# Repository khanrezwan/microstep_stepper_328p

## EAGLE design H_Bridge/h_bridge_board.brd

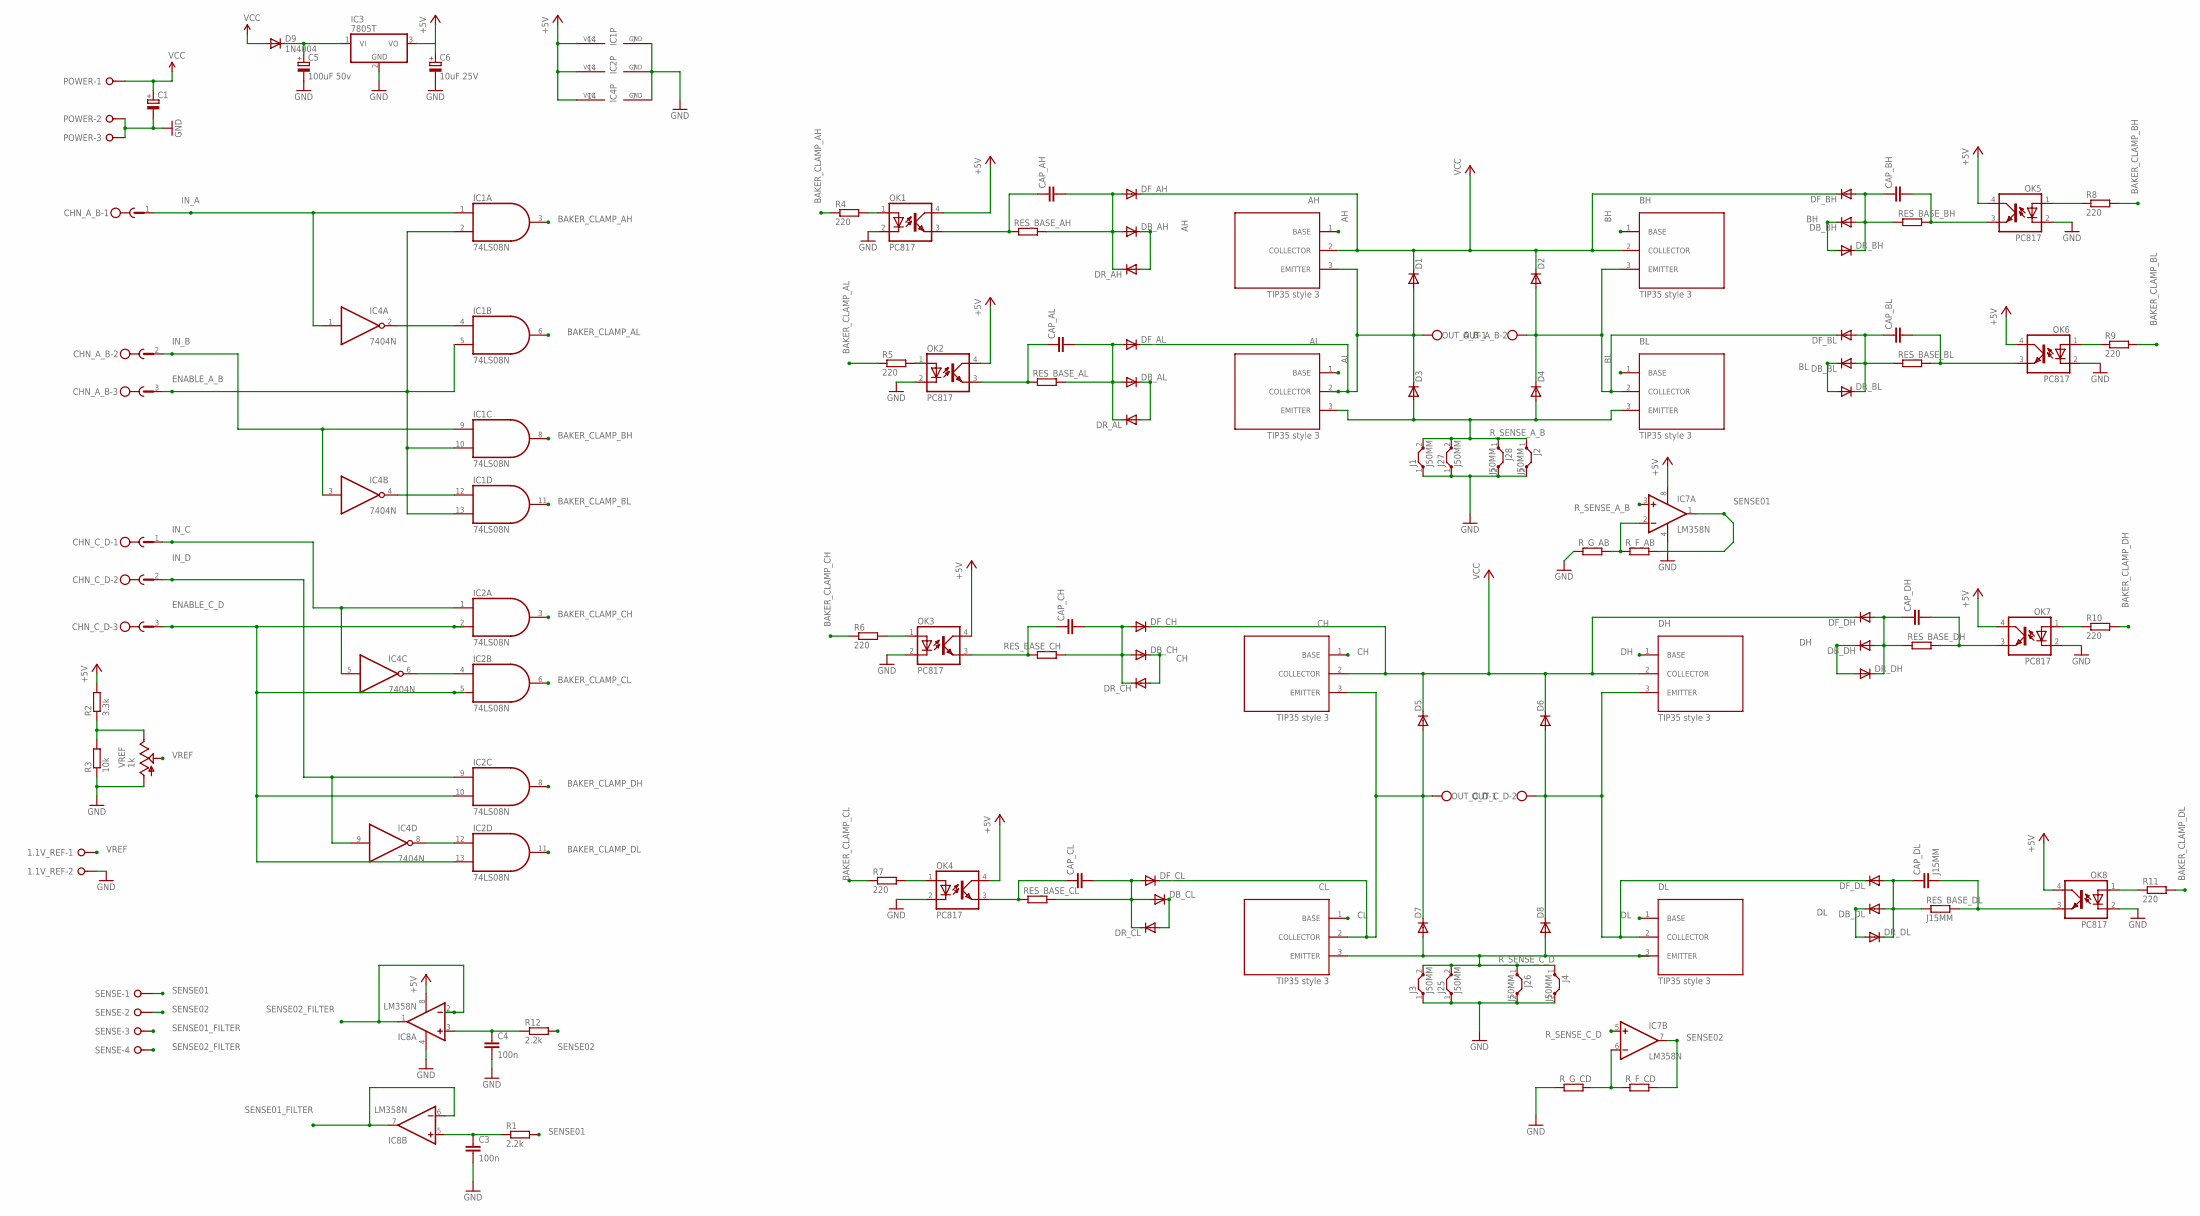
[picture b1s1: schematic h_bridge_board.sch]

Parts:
1.1V_REF: W237-02P; W237-132
AH: TIP35_STYLE3; P-TO247
AL: TIP35_STYLE3; P-TO247
BH: TIP35_STYLE3; P-TO247
BL: TIP35_STYLE3; P-TO247
C1: CPOL-EUE5-10.5; E5-10,5
C3, C4: 100n; C050-030X075
C5: 100uF 50v; E5-10,5
C6: 10uF 25V; E2,5-6
CAP_AH: C-EU050-030X075; C050-030X075
CAP_AL: C-EU050-030X075; C050-030X075
CAP_BH: C-EU050-030X075; C050-030X075
CAP_BL: C-EU050-030X075; C050-030X075
CAP_CH: C-EU050-030X075; C050-030X075
CAP_CL: C-EU050-030X075; C050-030X075
CAP_DH: C-EU050-030X075; C050-030X075
CAP_DL: J15MM; C050-030X075
CH: TIP35_STYLE3; P-TO247
CHN_A_B: W232-3
CHN_C_D: W232-3
CL: TIP35_STYLE3; P-TO247
D1, D2, D3, D4, D5, D6, D7, D8: DIODE-DO27-15; DO27-15
D9: 1N4004; DO41-10
DB_AH: DIODE-DO27-15; DO27-15
DB_AL: DIODE-DO27-15; DO27-15
DB_BH: DIODE-DO27-15; DO27-15
DB_BL: DIODE-DO27-15; DO27-15
DB_CH: DIODE-DO27-15; DO27-15
DB_CL: DIODE-DO27-15; DO27-15
DB_DH: DIODE-DO27-15; DO27-15
DB_DL: DIODE-DO27-15; DO27-15
DF_AH: DIODE-DO27-15; DO27-15
DF_AL: DIODE-DO27-15; DO27-15
DF_BH: DIODE-DO27-15; DO27-15
DF_BL: DIODE-DO27-15; DO27-15
DF_CH: DIODE-DO27-15; DO27-15
DF_CL: DIODE-DO27-15; DO27-15
DF_DH: DIODE-DO27-15; DO27-15
DF_DL: DIODE-DO27-15; DO27-15
DH: TIP35_STYLE3; P-TO247
DL: TIP35_STYLE3; P-TO247
DR_AH: DIODE-DO27-15; DO27-15
DR_AL: DIODE-DO27-15; DO27-15
DR_BH: DIODE-DO27-15; DO27-15
DR_BL: DIODE-DO27-15; DO27-15
DR_CH: DIODE-DO27-15; DO27-15
DR_CL: DIODE-DO27-15; DO27-15
DR_DH: DIODE-DO27-15; DO27-15
DR_DL: DIODE-DO27-15; DO27-15
IC1, IC2: 74LS08N; DIL14
IC3: 7805T; TO220H
IC4: 7404N; DIL14
IC7, IC8: LM358N; DIL08
J1, J2, J3, J4, J25, J26, J27, J28: J50MM; 50
OK1, OK2, OK3, OK4, OK5, OK6, OK7, OK8: PC817; DIL04
OUT_A_B: W237-102
OUT_C_D: W237-102
POWER: W237-3E
R1, R12: 2.2k; 0207/10
R2: 3.3k; 0207/10
R3: 10k; 0207/10
R4, R5, R6, R7, R8, R9, R10, R11: 220; 0207/10
RES_BASE_AH: R-EU_0207/10; 0207/10
RES_BASE_AL: R-EU_0207/10; 0207/10
RES_BASE_BH: R-EU_0207/10; 0207/10
RES_BASE_BL: R-EU_0207/10; 0207/10
RES_BASE_CH: R-EU_0207/10; 0207/10
RES_BASE_CL: R-EU_0207/10; 0207/10
RES_BASE_DH: R-EU_0207/10; 0207/10
RES_BASE_DL: J15MM; 0207/10
R_F_AB: R-EU_0207/10; 0207/10
R_F_CD: R-EU_0207/10; 0207/10
R_G_AB: R-EU_0207/10; 0207/10
R_G_CD: R-EU_0207/10; 0207/10
SENSE: W237-04P; W237-4P
VREF: 1k; B25U

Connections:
+5V: C6.+, IC1.14 (VCC), IC2.14 (VCC), IC3.3 (VO), IC4.14 (VCC), IC7.8 (V+), IC8.8 (V+), OK1.4 (COL), OK2.4 (COL), OK3.4 (COL), OK4.4 (COL), OK5.4 (COL), OK6.4 (COL), OK7.4 (COL), OK8.4 (COL), R2.2
AH: AH.1 (BASE), DB_AH.C, DR_AH.A
AL: AL.1 (BASE), DB_AL.C, DR_AL.A
BAKER_CLAMP_AH: IC1.3 (O), R4.1
BAKER_CLAMP_AL: IC1.6 (O), R5.1
BAKER_CLAMP_BH: IC1.8 (O), R8.2
BAKER_CLAMP_BL: IC1.11 (O), R9.2
BAKER_CLAMP_CH: IC2.3 (O), R6.1
BAKER_CLAMP_CL: IC2.6 (O), R7.1
BAKER_CLAMP_DH: IC2.8 (O), R10.2
BAKER_CLAMP_DL: IC2.11 (O), R11.2
BH: BH.1 (BASE), DB_BH.C, DR_BH.A
BL: BL.1 (BASE), DB_BL.C, DR_BL.A
CH: CH.1 (BASE), DB_CH.C, DR_CH.A
CL: CL.1 (BASE), DB_CL.C, DR_CL.A
DH: DB_DH.C, DH.1 (BASE), DR_DH.A
DL: DB_DL.C, DL.1 (BASE), DR_DL.A
ENABLE_A_B: CHN_A_B.3, IC1.2 (I1), IC1.5 (I1), IC1.10 (I1), IC1.13 (I1)
ENABLE_C_D: CHN_C_D.3, IC2.2 (I1), IC2.5 (I1), IC2.10 (I1), IC2.13 (I1)
GND: 1.1V_REF.2, C1.-, C3.2, C4.2, C5.-, C6.-, IC1.7 (GND), IC2.7 (GND), IC3.2 (GND), IC4.7 (GND), IC7.4 (V-), IC8.4 (V-), J1.1, J2.2, J3.1, J4.2, J25.1, J26.2, J27.1, J28.2, OK1.2 (C), OK2.2 (C), OK3.2 (C), OK4.2 (C), OK5.2 (C), OK6.2 (C), OK7.2 (C), OK8.2 (C), POWER.2, POWER.3, R3.1, R_G_AB.1, R_G_CD.1, VREF.A
IN_A: CHN_A_B.1, IC1.1 (I0), IC4.1 (I)
IN_B: CHN_A_B.2, IC1.9 (I0), IC4.3 (I)
IN_C: CHN_C_D.1, IC2.1 (I0), IC4.5 (I)
IN_D: CHN_C_D.2, IC2.9 (I0), IC4.9 (I)
unnamed: IC1.12 (I0), IC4.4 (O)
unnamed: R2.1, R3.2, VREF.E
unnamed: C5.+, D9.C, IC3.1 (VI)
unnamed: CAP_AL.2, DB_AL.A, DF_AL.A, DR_AL.C, RES_BASE_AL.2
unnamed: CAP_CH.2, DB_CH.A, DF_CH.A, DR_CH.C, RES_BASE_CH.1
unnamed: CAP_BL.1, DB_BL.A, DF_BL.A, DR_BL.C, RES_BASE_BL.1
unnamed: CAP_DH.1, DB_DH.A, DF_DH.A, DR_DH.C, RES_BASE_DH.1
unnamed: IC2.4 (I0), IC4.6 (O)
unnamed: OK1.1 (A), R4.2
unnamed: IC2.12 (I0), IC4.8 (O)
unnamed: OK2.1 (A), R5.2
unnamed: OK3.1 (A), R6.2
unnamed: IC7.6 (-IN), R_F_CD.1, R_G_CD.2
unnamed: OK4.1 (A), R7.2
unnamed: IC7.2 (-IN), R_F_AB.1, R_G_AB.2
unnamed: CAP_CL.2, DB_CL.A, DF_CL.A, DR_CL.C, RES_BASE_CL.2
unnamed: CAP_AH.2, DB_AH.A, DF_AH.A, DR_AH.C, RES_BASE_AH.2
unnamed: CAP_BH.1, DB_BH.A, DF_BH.A, DR_BH.C, RES_BASE_BH.1
unnamed: IC1.4 (I0), IC4.2 (O)
unnamed: OK8.1 (A), R11.1
unnamed: CAP_DL.1, DB_DL.A, DF_DL.A, DR_DL.C, RES_BASE_DL.1
unnamed: OK7.1 (A), R10.1
unnamed: OK6.1 (A), R9.1
unnamed: OK5.1 (A), R8.1
unnamed: CAP_DL.2, OK8.3 (EMIT), RES_BASE_DL.2
unnamed: CAP_BH.2, OK5.3 (EMIT), RES_BASE_BH.2
unnamed: CAP_BL.2, OK6.3 (EMIT), RES_BASE_BL.2
unnamed: CAP_DH.2, OK7.3 (EMIT), RES_BASE_DH.2
unnamed: CAP_CL.1, OK4.3 (EMIT), RES_BASE_CL.1
unnamed: CAP_CH.1, OK3.3 (EMIT), RES_BASE_CH.2
unnamed: CAP_AL.1, OK2.3 (EMIT), RES_BASE_AL.1
unnamed: CAP_AH.1, OK1.3 (EMIT), RES_BASE_AH.1
unnamed: C3.1, IC8.5 (+IN), R1.1
unnamed: C4.1, IC8.3 (+IN), R12.1
OUT_A: AH.3 (EMITTER), AL.2 (COLLECTOR), D1.A, D3.C, DF_AL.C, OUT_A_B.1
OUT_B: BH.3 (EMITTER), BL.2 (COLLECTOR), D2.A, D4.C, DF_BL.C, OUT_A_B.2
OUT_C: CH.3 (EMITTER), CL.2 (COLLECTOR), D5.A, D7.C, DF_CL.C, OUT_C_D.1
OUT_D: D6.A, D8.C, DF_DL.C, DH.3 (EMITTER), DL.2 (COLLECTOR), OUT_C_D.2
R_SENSE_A_B: AL.3 (EMITTER), BL.3 (EMITTER), D3.A, D4.A, IC7.3 (+IN), J1.2, J2.1, J27.2, J28.1
R_SENSE_C_D: CL.3 (EMITTER), D7.A, D8.A, DL.3 (EMITTER), IC7.5 (+IN), J3.2, J4.1, J25.2, J26.1
SENSE01: IC7.1 (OUT), R1.2, R_F_AB.2, SENSE.1
SENSE01_FILTER: IC8.6 (-IN), IC8.7 (OUT), SENSE.3
SENSE02: IC7.7 (OUT), R12.2, R_F_CD.2, SENSE.2
SENSE02_FILTER: IC8.1 (OUT), IC8.2 (-IN), SENSE.4
VCC: AH.2 (COLLECTOR), BH.2 (COLLECTOR), C1.+, CH.2 (COLLECTOR), D1.C, D2.C, D5.C, D6.C, D9.A, DF_AH.C, DF_BH.C, DF_CH.C, DF_DH.C, DH.2 (COLLECTOR), POWER.1
VREF: 1.1V_REF.1, VREF.S

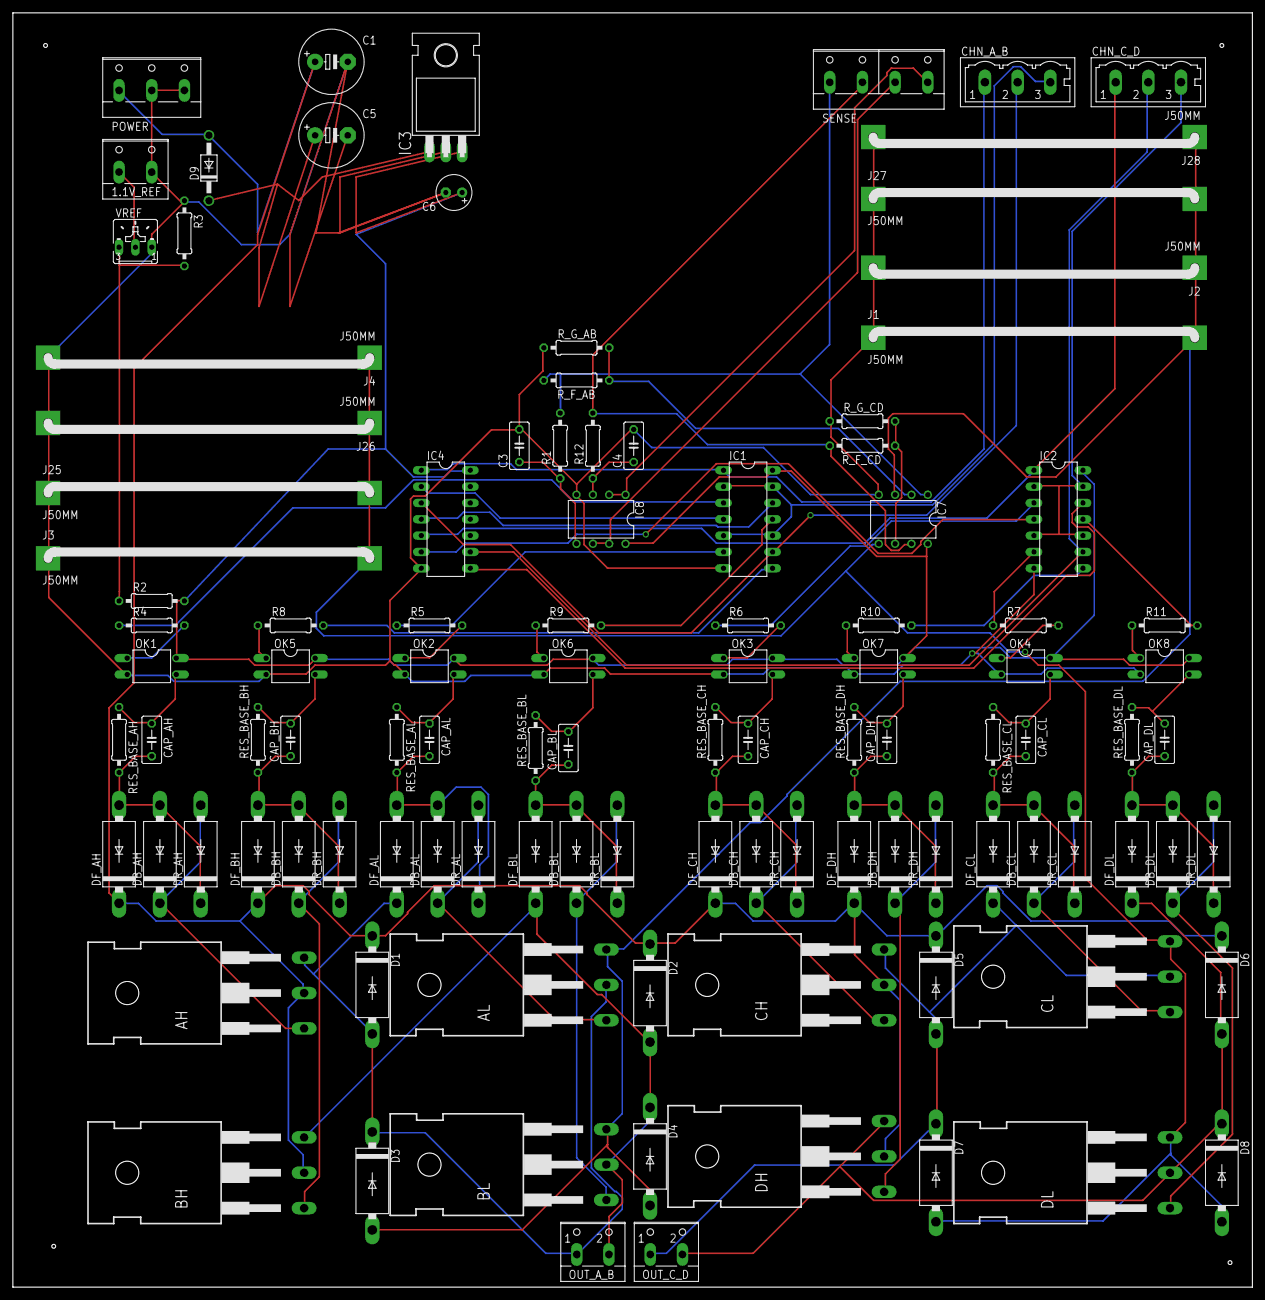
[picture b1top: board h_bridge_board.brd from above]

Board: 2 copper layers, 192.7 x 198.1 mm, 108 parts (0 on the bottom side), 70 nets.

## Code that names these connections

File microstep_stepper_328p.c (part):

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#define NotCNT1 6 //Phase1_B will goto 408(AND gate) 7408(AND gate) pin 9.
#define CNT2 5 //Phase2_A will goto 7408(AND gate) pin 5.
#define NotCNT2 4 //Phase2_B will goto 7408(AND gate) pin 12.
#define Enable_A_B 3 //Enable H Bridge 1 i.e.. 1A and 1B Enable_A_B
#define Enable_C_D 2 //Enable H Bridge 1 i.e.. 2A and 2B Enable_C_D


///defining bits for shift reg to 74157 interface
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 * H-bridge Sense resistor -> AVR
 *
 * */
#define SENSE01 PC0
#define SENSE02 PC1
//Todo change Shift register port assignment
#define VREF PC2  //VREF is connected with a 1k/10K pot. this pot is part of a volatge divider. i.e. pot will give us 0v->1.1V
/*
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
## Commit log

2016-12-12 generating 40kHz PWM
2016-12-12 Added eaglecad library for tip35 style 3
2016-12-13 added mode resource. proteus file for design
2016-12-14 added shift reg functions. added proteus simulation
2016-12-15 proteus design nearly complete. started decay mode table in ods file
2016-12-15 all lookup table complete in ods file. updated circuit. uses one less shift reg. shift reg functions added into header
2016-12-15 adding codes
2016-12-16 fixed circuit. step tables in separate header file
2016-12-16 added debug print. added timer2 kernel. added adc0 skeleton code. added current sensing doc. All subject to test
2016-12-17 added a simulation for opamp non inversting
2016-12-18 added eagle schematic for h bridge dev board
2016-12-18 Adding gitignore
2016-12-18 removing some more unneeded files
2016-12-19 minor update in schematic
2016-12-19 dev board schematic nearly complete
2016-12-20 ADC code working. dev board schematic needs final check
2016-12-21 adding couple resource pdfs
2016-12-21 Added L298 config in ADC for testing.ADC results are stored in array
2016-12-22 updated git ignore
2016-12-22 caught massive bug in decay mode table
2016-12-22 Trouble shooting the bug. added step_test() offline driver
2016-12-23 offline test forward ready for testing
2016-12-23 minor change
2016-12-23 Major schematic change. swapped few pins. code needs update
2016-12-24 minor schematic update
2016-12-24 added opto coupler in schematic
2016-12-25 reduced jumper size in schematic
2016-12-25 prili board placement
2016-12-26 testing at lab. fix sin table
2016-12-26 microstep works with l298 at 20KHz. ipdate schematic with active RC low pass filters
2016-12-27 adding ADC code
2016-12-27 Hbridge spearate schematic added
2016-12-27 added board file
2016-12-28 started desiging proteus mosfet h bridge
2016-12-29 designing mosfet h bridge
2016-12-29 working on mosfet board
2016-12-30 working on mosfet h bridge
2017-01-03 PCB Layoput
2017-01-04 mosfet
2017-01-04 Mosfet H bridge almost done
2017-01-04 minor change in mosfet pcb
    still got to add the silk screen
2017-01-05 Added Silk screen
2017-01-05 Added printer output *.PRN
2017-01-05 Added mirrored and normal *.prn files for all ouputs

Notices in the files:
parts and their libraries:
SparkFun-Aesthetics: Licensing: Creative Commons ShareAlike 4.0 International - https://creativecommons.org/licenses/by-sa/4.0
